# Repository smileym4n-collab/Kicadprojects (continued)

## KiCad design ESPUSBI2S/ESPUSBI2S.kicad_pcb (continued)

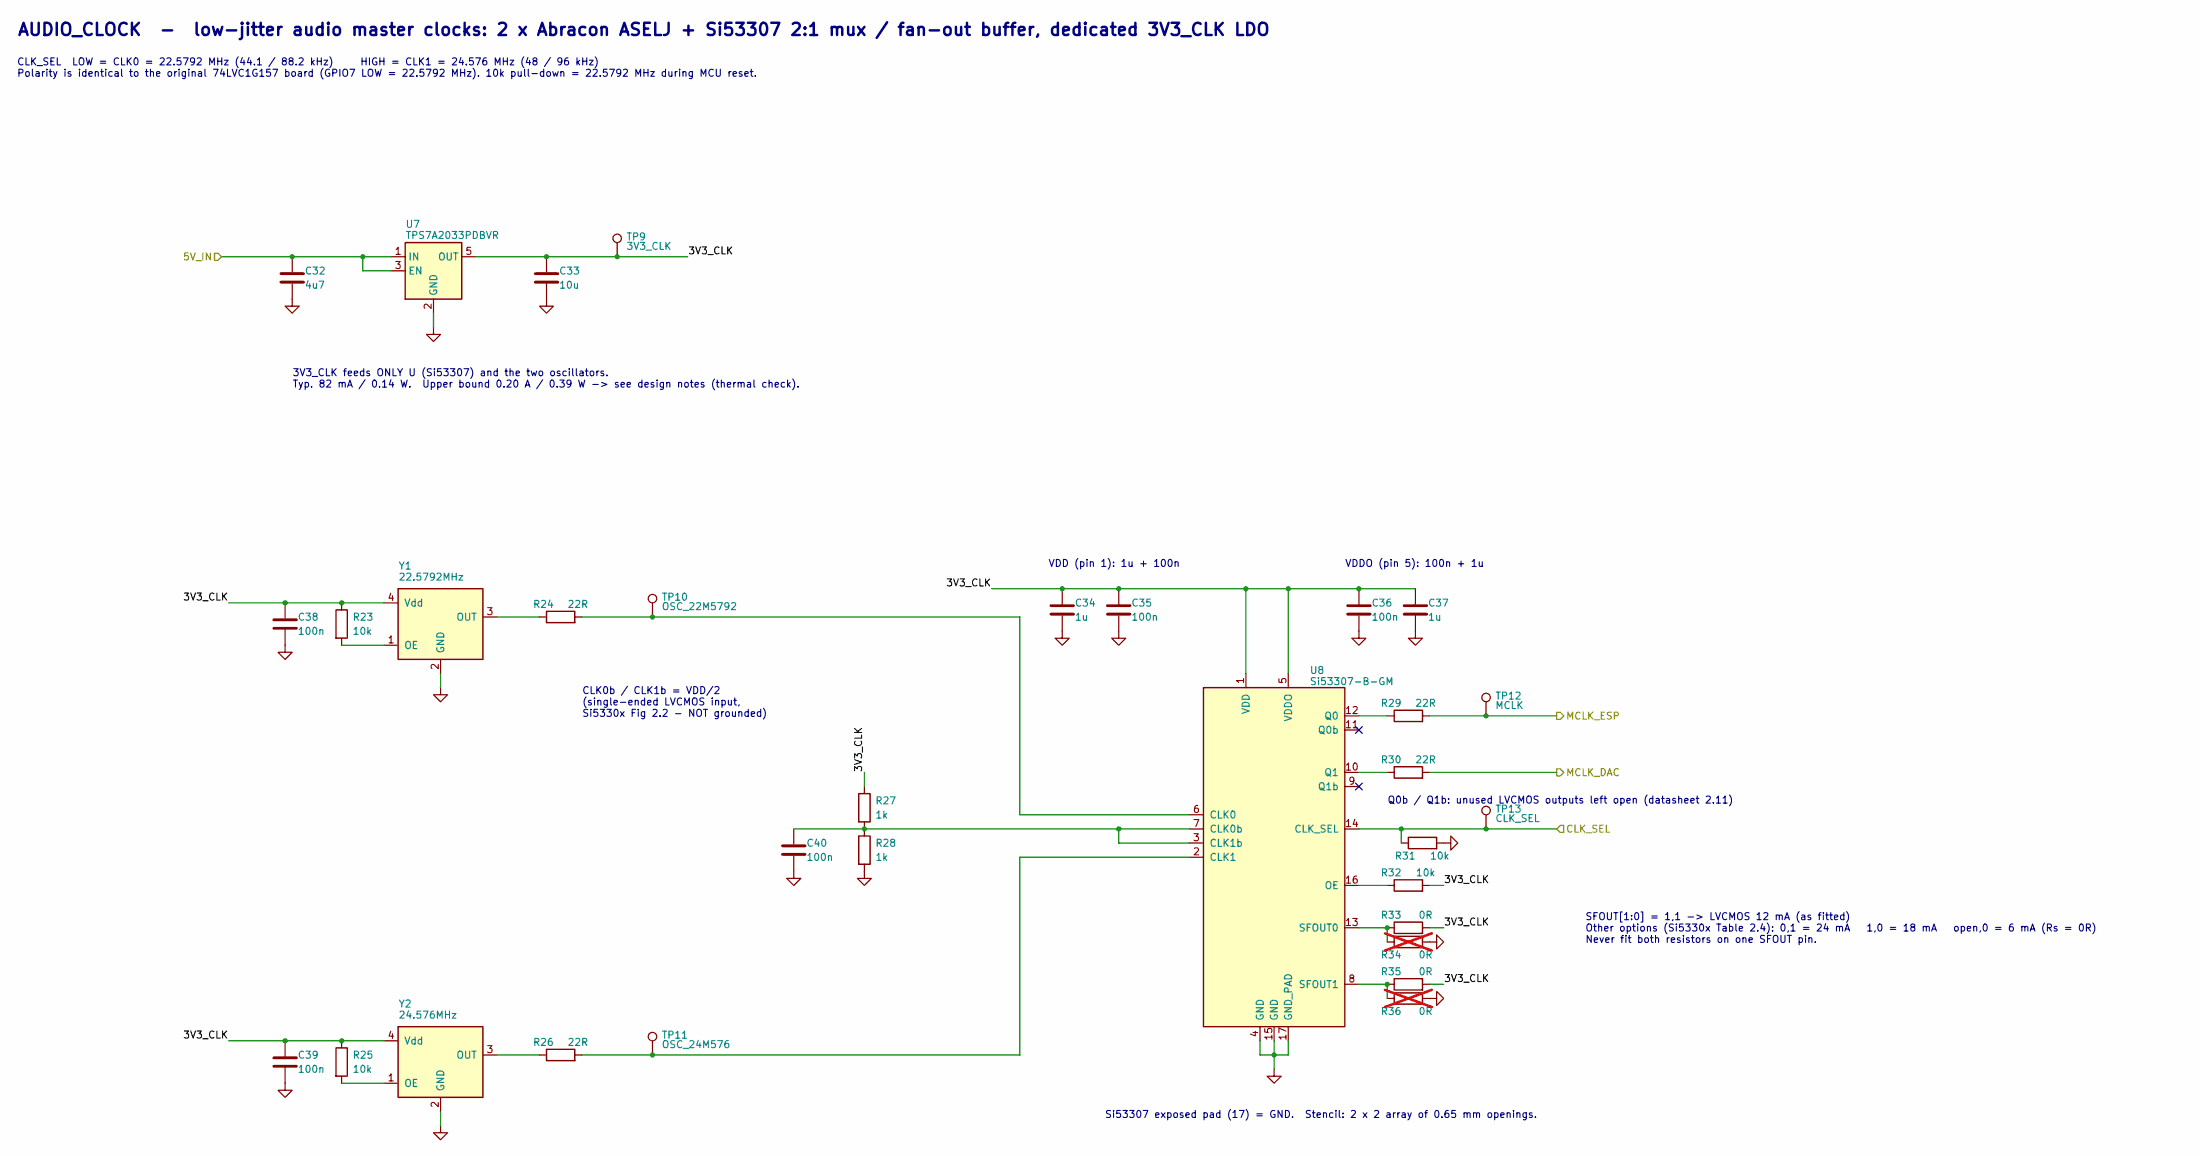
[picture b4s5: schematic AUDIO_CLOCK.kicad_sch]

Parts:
C32: 4u7; C_0805_2012Metric; MPN CL21A475KAQNNNE
C33: 10u; C_1206_3216Metric; MPN TMK316B7106KL-TD
C34, C37: 1u; C_0805_2012Metric; MPN C0805C105K3RACTU
C35, C36, C38, C39, C40: 100n; C_0603_1608Metric; MPN MC0603B104K500CT
R23, R25, R31, R32: 10k; R_0603_1608Metric; MPN RC0603FR-0710KL
R24, R26, R29, R30: 22R; R_0603_1608Metric; MPN RK73B1JTTD220J
R27, R28: 1k; R_0603_1608Metric; MPN RC0603FR-101KL
R33, R35: 0R; R_0805_2012Metric; MPN RK73Z2ATTD
R34, R36: 0R; R_0805_2012Metric; MPN RK73Z2ATTD; not fitted
TP9: 3V3_CLK; TestPoint_Pad_D1.0mm
TP10: OSC_22M5792; TestPoint_Pad_D1.0mm
TP11: OSC_24M576; TestPoint_Pad_D1.0mm
TP12: MCLK; TestPoint_Pad_D1.0mm
TP13: CLK_SEL; TestPoint_Pad_D1.0mm
U7: TPS7A2033PDBVR; SOT-23-5; MPN TPS7A2033PDBVR
U8: Si53307-B-GM; Si53307_QFN-16-1EP_3x3mm_P0.5mm_EP1.8x1.8mm; MPN Si53307-B-GM
Y1: 22.5792MHz; Abracon_ASELJ_3.2x2.5mm; MPN ASELJ-E-22.5792MHZ-L-R-T
Y2: 24.576MHz; Abracon_ASELJ_3.2x2.5mm; MPN ASELJ-E-24.576MHZ-L-R-T

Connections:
/USB_AUDIO_UAC2/5V_IN: C32.1, U7.1 (IN), U7.3 (EN); also elsewhere on the board
/USB_AUDIO_UAC2/AUDIO_CLOCK/3V3_CLK: C33.1, C34.1, C35.1, C36.1, C37.1, C38.1, C39.1, R23.1, R25.1, R27.1, R32.2, R33.2, R35.2, TP9.1 (1_1), U7.5 (OUT), U8.1 (VDD), U8.5 (VDDO), Y1.4 (Vdd), Y2.4 (Vdd)
/USB_AUDIO_UAC2/AUDIO_CLOCK/CLK_SEL: R31.1, TP13.1 (1_1), U8.14 (CLK_SEL); also elsewhere on the board
/USB_AUDIO_UAC2/AUDIO_CLOCK/MCLK_ESP: R29.2, TP12.1 (1_1); also elsewhere on the board
/USB_AUDIO_UAC2/MCLK_DAC: R30.2; also elsewhere on the board
GND: C32.2, C33.2, C34.2, C35.2, C36.2, C37.2, C38.2, C39.2, C40.2, R28.2, R31.2, R34.2, R36.2, U7.2 (GND), U8.4 (GND), U8.15 (GND), U8.17 (GND_PAD), Y1.2 (GND), Y2.2 (GND); also elsewhere on the board
unnamed: R24.2, TP10.1 (1_1), U8.6 (CLK0)
unnamed: C40.1, R27.2, R28.1, U8.3 (CLK1b), U8.7 (CLK0b)
unnamed: R26.2, TP11.1 (1_1), U8.2 (CLK1)
unnamed: R32.1, U8.16 (OE)
unnamed: R29.1, U8.12 (Q0)
unnamed: R30.1, U8.10 (Q1)
unnamed: R33.1, R34.1, U8.13 (SFOUT0)
unnamed: R35.1, R36.1, U8.8 (SFOUT1)
unnamed: R23.2, Y1.1 (OE)
unnamed: R24.1, Y1.3 (OUT)
unnamed: R25.2, Y2.1 (OE)
unnamed: R26.1, Y2.3 (OUT)

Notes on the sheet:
CLK0b / CLK1b = VDD/2 (single-ended LVCMOS input, Si5330x Fig 2.2 - NOT grounded)
AUDIO_CLOCK - low-jitter audio master clocks: 2 x Abracon ASELJ + Si53307 2:1 mux / fan-out buffer, dedicated 3V3_CLK LDO
CLK_SEL LOW = CLK0 = 22.5792 MHz (44.1 / 88.2 kHz) HIGH = CLK1 = 24.576 MHz (48 / 96 kHz) Polarity is identical to the original 74LVC1G157 board (GPIO7 LOW = 22.5792 MHz). 10k pull-down = 22.5792 MHz during MCU reset.
SFOUT[1:0] = 1,1 -> LVCMOS 12 mA (as fitted) Other options (Si5330x Table 2.4): 0,1 = 24 mA 1,0 = 18 mA open,0 = 6 mA (Rs = 0R) Never fit both resistors on one SFOUT pin.
Q0b / Q1b: unused LVCMOS outputs left open (datasheet 2.11)
VDD (pin 1): 1u + 100n
VDDO (pin 5): 100n + 1u
Si53307 exposed pad (17) = GND. Stencil: 2 x 2 array of 0.65 mm openings.
3V3_CLK feeds ONLY U (Si53307) and the two oscillators. Typ. 82 mA / 0.14 W. Upper bound 0.20 A / 0.39 W -> see design notes (thermal check).

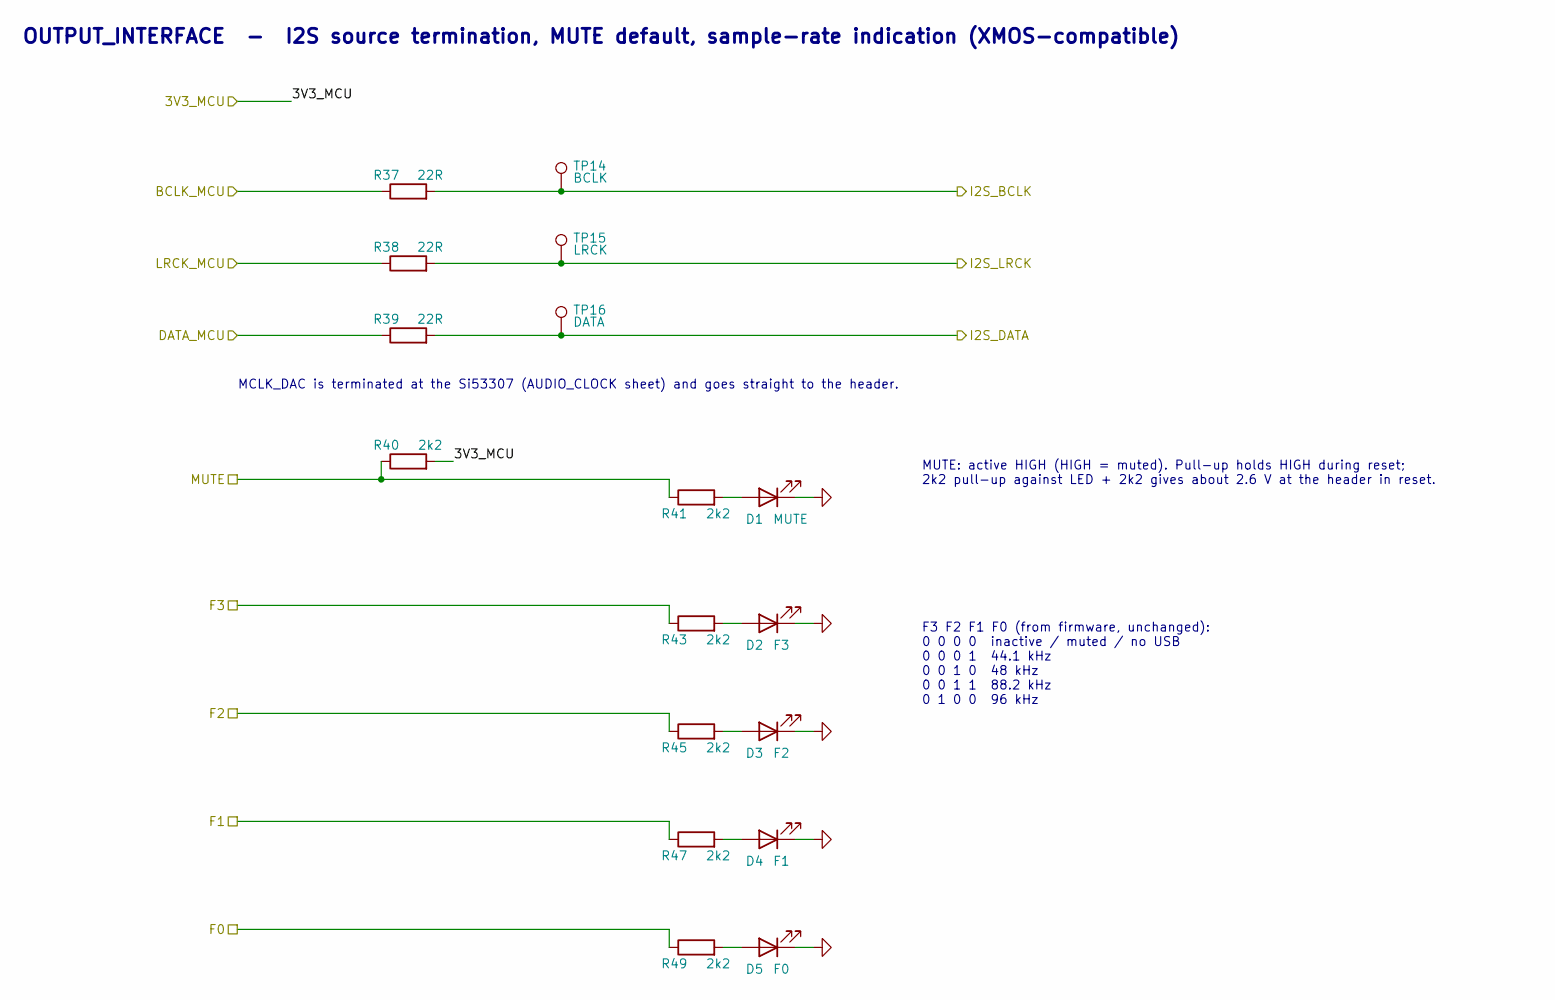
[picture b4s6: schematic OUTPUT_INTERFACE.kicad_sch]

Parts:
D1: MUTE; LED_0805_2012Metric; MPN KP-2012EC
D2: F3; LED_0805_2012Metric; MPN KP-2012EC
D3: F2; LED_0805_2012Metric; MPN KP-2012EC
D4: F1; LED_0805_2012Metric; MPN KP-2012EC
D5: F0; LED_0805_2012Metric; MPN KP-2012EC
R37, R38, R39: 22R; R_0603_1608Metric; MPN RK73B1JTTD220J
R40, R41, R43, R45, R47, R49: 2k2; R_0603_1608Metric; MPN RC0603JR-072K2L
TP14: BCLK; TestPoint_Pad_D1.0mm
TP15: LRCK; TestPoint_Pad_D1.0mm
TP16: DATA; TestPoint_Pad_D1.0mm

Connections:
/USB_AUDIO_UAC2/3V3_MCU: R40.2; also elsewhere on the board
/USB_AUDIO_UAC2/ESP32_UAC2/BCLK_MCU: R37.1; also elsewhere on the board
/USB_AUDIO_UAC2/ESP32_UAC2/DATA_MCU: R39.1; also elsewhere on the board
/USB_AUDIO_UAC2/ESP32_UAC2/LRCK_MCU: R38.1; also elsewhere on the board
/USB_AUDIO_UAC2/F0: R49.1; also elsewhere on the board
/USB_AUDIO_UAC2/F1: R47.1; also elsewhere on the board
/USB_AUDIO_UAC2/F2: R45.1; also elsewhere on the board
/USB_AUDIO_UAC2/F3: R43.1; also elsewhere on the board
/USB_AUDIO_UAC2/I2S_BCLK: R37.2, TP14.1 (1_1); also elsewhere on the board
/USB_AUDIO_UAC2/I2S_DATA: R39.2, TP16.1 (1_1); also elsewhere on the board
/USB_AUDIO_UAC2/I2S_LRCK: R38.2, TP15.1 (1_1); also elsewhere on the board
/USB_AUDIO_UAC2/MUTE: R40.1, R41.1; also elsewhere on the board
GND: D1.1 (K), D2.1 (K), D3.1 (K), D4.1 (K), D5.1 (K); also elsewhere on the board
unnamed: D1.2 (A), R41.2
unnamed: D2.2 (A), R43.2
unnamed: D3.2 (A), R45.2
unnamed: D4.2 (A), R47.2
unnamed: D5.2 (A), R49.2

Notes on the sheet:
MCLK_DAC is terminated at the Si53307 (AUDIO_CLOCK sheet) and goes straight to the header.
MUTE: active HIGH (HIGH = muted). Pull-up holds HIGH during reset; 2k2 pull-up against LED + 2k2 gives about 2.6 V at the header in reset.
F3 F2 F1 F0 (from firmware, unchanged): 0 0 0 0 inactive / muted / no USB 0 0 0 1 44.1 kHz 0 0 1 0 48 kHz 0 0 1 1 88.2 kHz 0 1 0 0 96 kHz
OUTPUT_INTERFACE - I2S source termination, MUTE default, sample-rate indication (XMOS-compatible)

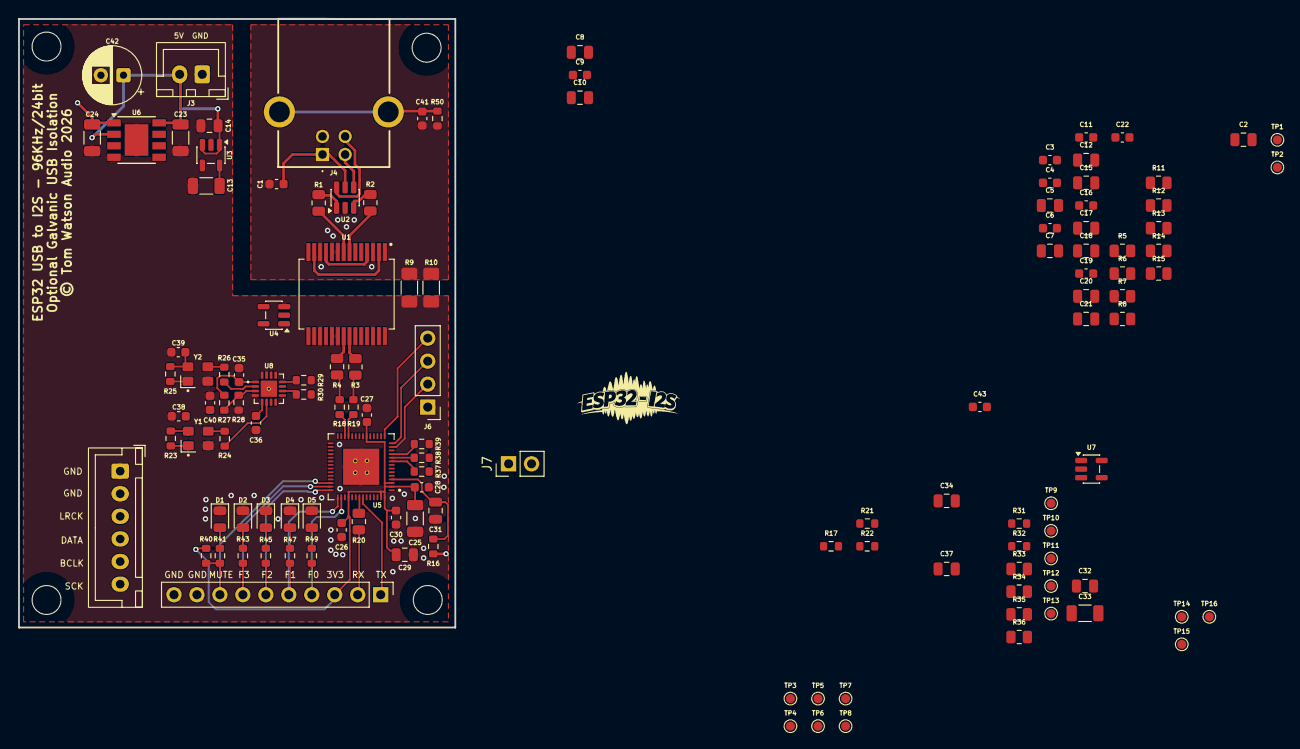
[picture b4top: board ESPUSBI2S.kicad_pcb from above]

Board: 4 copper layers, 48.3 x 67.3 mm, 130 parts (0 on the bottom side), 68 nets.

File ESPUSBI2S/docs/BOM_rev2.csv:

Refs,Qty,Value,MPN,Footprint,Config A (isolated),Config B (non-isolated),In stock,Source,Description
U1,1,ISOUSB211DPR,ISOUSB211DPR,ESPUSBI2S:ISOUSB211_DP0028A_SSOP-28_7.5x10.3mm_P0.65mm,FIT,DNP,0,BUY,"Isolated USB 2.0 HS/FS/LS repeater, 28-SSOP (DP)"
U2,1,USBLC6-2SC6,USBLC6-2SC6,Package_TO_SOT_SMD:SOT-23-6,FIT,FIT,5,inventory,"Very low capacitance ESD protection diode, 2 data-line, SOT-23-6"
C1 C26 C27 C28 C30 C35 C36 C38 C39 C40 C41 C43,12,100n,MC0603B104K500CT,Capacitor_SMD:C_0603_1608Metric,FIT,FIT,961,inventory,5 V input HF decoupling (as original board) - 100 nF 50 V X7R 1608
C2 C14,2,4u7,CL21A475KAQNNNE,Capacitor_SMD:C_0805_2012Metric,FIT,DNP,37,inventory,3V3_ISO LDO input 4.7 uF 16 V X7R - 4.7 uF 25 V X5R 2012
C3 C4 C6 C9 C11 C16 C19,7,100n,MC0603B104K500CT,Capacitor_SMD:C_0603_1608Metric,FIT,DNP,961,inventory,"V1P8V2 decoupling at pin 18 (TI 8.3: 2 uF + 0.1 uF + 10 nF, smallest closest) - 100 nF 50 V X7R 1608"
C5 C8 C17 C20,4,2u2,CL21B225KPFNNNE,Capacitor_SMD:C_0805_2012Metric,FIT,DNP,54,inventory,"V1P8V2 decoupling at pin 18 (TI 8.3: 2 uF + 0.1 uF + 10 nF, smallest closest) - 2.2 uF 10 V X7R 2012"
C7 C10 C15 C18,4,10n,0805B103K500CT,Capacitor_SMD:C_0805_2012Metric,FIT,DNP,13,inventory,"V1P8V2 decoupling at pin 18 (TI 8.3: 2 uF + 0.1 uF + 10 nF, smallest closest) - 10 nF 50 V X7R 2012"
U3,1,TPS7A2033PDBVR,TPS7A2033PDBVR,Package_TO_SOT_SMD:SOT-23-5,FIT,DNP,6,inventory,"300 mA LDO, fixed 3.3 V (ISOUSB211 local side only)"
C12,1,1u,C0805C105K3RACTU,Capacitor_SMD:C_0805_2012Metric,FIT,DNP,87,inventory,VBUS2 / VCC2 decoupling - 1 uF 25 V X7R 2012
C13,1,10u,TMK316B7106KL-TD,Capacitor_SMD:C_1206_3216Metric,FIT,DNP,43,inventory,3V3_ISO LDO output 10 uF 10 V X7R - 10 uF 25 V X7R 3216
R1 R2 R3 R4 R11,5,0R,RK73Z2ATTD,Resistor_SMD:R_0805_2012Metric,FIT,DNP,64,inventory,VBUS_DET source select: ISOUSB211 V1OK (config A)
R5 R6 R7 R8 R9 R10 R15,7,0R,RK73Z2ATTD,Resistor_SMD:R_0805_2012Metric,DNP,FIT,64,inventory,VBUS_DET source select: divider + buffer (config B)
R12,1,100k,RK73B2ATTE104J,Resistor_SMD:R_0805_2012Metric,FIT,FIT,44,inventory,VBUS_DET pull-down (defined LOW with no source link fitted)
U4,1,74LVC1G17,SN74LVC1G17DBVR,Package_TO_SOT_SMD:SOT-23-5,DNP,FIT,1,inventory,Schmitt buffer with Ioff (no back-feed into the MCU rail when local power is off)
R13,1,33k,MCWR08X3302FTL,Resistor_SMD:R_0805_2012Metric,DNP,FIT,100,inventory,VBUS divider top (the only part bridging the barrier in config B)
R14,1,47k,RMCF0805FT47K0,Resistor_SMD:R_0805_2012Metric,DNP,FIT,93,inventory,"VBUS divider bottom (ratio 0.588: 4.35 V -> 2.56 V, 5.5 V -> 3.23 V)"
C21,1,10n,0805B103K500CT,Capacitor_SMD:C_0805_2012Metric,DNP,FIT,13,inventory,VBUS detect filter - 10 nF 50 V X7R 2012
C22,1,100n,MC0603B104K500CT,Capacitor_SMD:C_0603_1608Metric,DNP,FIT,961,inventory,74LVC1G17 decoupling - 100 nF 50 V X7R 1608
U5,1,ESP32-S3-PICO-1-N8R2,ESP32-S3-PICO-1-N8R2,ESPUSBI2S:ESP32-S3-PICO-1_LGA-56-1EP_7x7mm_P0.4mm,FIT,FIT,,BUY,"ESP32-S3 SiP, 8 MB quad flash, 2 MB quad PSRAM, 40 MHz crystal, LGA56 7x7 mm"
U6,1,AP7361C-33SP-13,AP7361C-33SP-13,Package_SO:Diodes_SO-8EP,FIT,FIT,,BUY,"1 A LDO, fixed 3.3 V, enable, SO-8EP"
C23 C25 C33,3,10u,TMK316B7106KL-TD,Capacitor_SMD:C_1206_3216Metric,FIT,FIT,43,inventory,10 uF 10 V X7R - 10 uF 25 V X7R 3216
C24,1,22u,EMK316BB7226ML-T,Capacitor_SMD:C_1206_3216Metric,FIT,FIT,,BUY,22 uF 16 V X7R 3216 (regulator output) - 22 uF 16 V X7R 3216
C29 C31 C34 C37,4,1u,C0805C105K3RACTU,Capacitor_SMD:C_0805_2012Metric,FIT,FIT,87,inventory,1 uF 16 V X7R - at VDDO pin 5 - 1 uF 25 V X7R 2012
R16 R17 R21 R22 R23 R25 R31 R32 R42 R44 R46 R48,12,10k,RC0603FR-0710KL,Resistor_SMD:R_0603_1608Metric,FIT,FIT,53,inventory,Sample-rate line pull-down: 0000 (inactive) while the MCU is in reset (new in rev 2)
R18 R19 R24 R26 R29 R30 R37 R38 R39,9,22R,RK73B1JTTD220J,Resistor_SMD:R_0603_1608Metric,FIT,FIT,139,inventory,I2S source termination - place at the MCU pin (as original board)
R20,1,470R,ASC0805-470RFT5,Resistor_SMD:R_0805_2012Metric,FIT,FIT,86,inventory,U0TXD series resistor (Espressif guideline suggests 499R; 470R from stock)
U7,1,TPS7A2033PDBVR,TPS7A2033PDBVR,Package_TO_SOT_SMD:SOT-23-5,FIT,FIT,6,inventory,"300 mA low-noise LDO, fixed 3.3 V (clock rail only)"
C32,1,4u7,CL21A475KAQNNNE,Capacitor_SMD:C_0805_2012Metric,FIT,FIT,37,inventory,4.7 uF 16 V X7R - 4.7 uF 25 V X5R 2012
U8,1,Si53307-B-GM,Si53307-B-GM,ESPUSBI2S:Si53307_QFN-16-1EP_3x3mm_P0.5mm_EP1.8x1.8mm,FIT,FIT,,BUY,"2:1 glitchless clock mux + 2-output universal buffer, low additive jitter, 16-QFN 3x3 mm"
Y1,1,22.5792MHz,ASELJ-E-22.5792MHZ-L-R-T,ESPUSBI2S:Abracon_ASELJ_3.2x2.5mm,FIT,FIT,,BUY,"Low-jitter 3.3 V CMOS crystal oscillator, 3.2 x 2.5 mm, OE active high (open = enabled)"
Y2,1,24.576MHz,ASELJ-E-24.576MHZ-L-R-T,ESPUSBI2S:Abracon_ASELJ_3.2x2.5mm,FIT,FIT,,BUY,"Low-jitter 3.3 V CMOS crystal oscillator, 3.2 x 2.5 mm, OE active high (open = enabled)"
R27 R28,2,1k,RC0603FR-101KL,Resistor_SMD:R_0603_1608Metric,FIT,FIT,99,inventory,CLK0b/CLK1b bias divider to VDD/2 (Si5330x Fig 2.2)
R33 R35,2,0R,RK73Z2ATTD,Resistor_SMD:R_0805_2012Metric,FIT,FIT,64,inventory,SFOUT1 strap HIGH (fitted): LVCMOS 12 mA drive with SFOUT[1:0] = 11
R34 R36,2,0R,RK73Z2ATTD,Resistor_SMD:R_0805_2012Metric,DNP (option),DNP (option),64,inventory,SFOUT1 strap LOW (alternative drive strength) - DNP
R40 R41 R43 R45 R47 R49,6,2k2,RC0603JR-072K2L,Resistor_SMD:R_0603_1608Metric,FIT,FIT,37,inventory,LED current limit (as original board)
D1,1,MUTE,KP-2012EC,LED_SMD:LED_0805_2012Metric,FIT,FIT,9,inventory,"Red indicator LED 2012, Kingbright KP-2012EC (optional - DNP for integrated use)"
D2,1,F3,KP-2012EC,LED_SMD:LED_0805_2012Metric,FIT,FIT,9,inventory,"Red indicator LED 2012, Kingbright KP-2012EC (optional - DNP for integrated use)"
D3,1,F2,KP-2012EC,LED_SMD:LED_0805_2012Metric,FIT,FIT,9,inventory,"Red indicator LED 2012, Kingbright KP-2012EC (optional - DNP for integrated use)"
D4,1,F1,KP-2012EC,LED_SMD:LED_0805_2012Metric,FIT,FIT,9,inventory,"Red indicator LED 2012, Kingbright KP-2012EC (optional - DNP for integrated use)"
D5,1,F0,KP-2012EC,LED_SMD:LED_0805_2012Metric,FIT,FIT,9,inventory,"Red indicator LED 2012, Kingbright KP-2012EC (optional - DNP for integrated use)"
J1,1,I2S OUT,,Connector_JST:JST_XH_B6B-XH-A_1x06_P2.50mm_Vertical,FIT,FIT,,not tracked in inventory,Connector (pin-out unchanged from the original board)
J2,1,STATUS / UART,,Connector_PinHeader_2.54mm:PinHeader_1x10_P2.54mm_Vertical,FIT,FIT,,not tracked in inventory,Connector (pin-out unchanged from the original board)
J6,1,COMM,,Connector_PinHeader_2.54mm:PinHeader_1x04_P2.54mm_Vertical,FIT,FIT,,not tracked in inventory,Connector (pin-out unchanged from the original board)
J7,1,BOOT,,Connector_PinHeader_2.54mm:PinHeader_1x02_P2.54mm_Vertical,FIT,FIT,,not tracked in inventory,"BOOT jumper: 2-pin 2.54 mm header, GPIO0 to GND; fit shunt while applying power for ROM download mode"
J4,1,USB CONNECTOR,,Custom:USBC,FIT,FIT,,not tracked in inventory,USB receptacle (footprint and pin mapping unchanged from the original board)
R50,1,1M,RC0603FR-101ML,Resistor_SMD:R_0603_1608Metric,FIT,FIT,90,inventory,USB shield bleed to GND_USB (as original board)
J3,1,POWER IN 5V,,Connector_JST:JST_XH_B2B-XH-A_1x02_P2.50mm_Vertical,FIT,FIT,,not tracked in inventory,"Regulated 5 V DC input (pin 1 GND, pin 2 +5 V - unchanged)"
C42,1,220u,EEUFR1C221B,Capacitor_THT:CP_Radial_D6.3mm_P2.50mm,FIT,FIT,10,inventory,"5 V input reservoir 220 uF 16 V Panasonic FR, 6.3 x 11.2 mm (as original board)"

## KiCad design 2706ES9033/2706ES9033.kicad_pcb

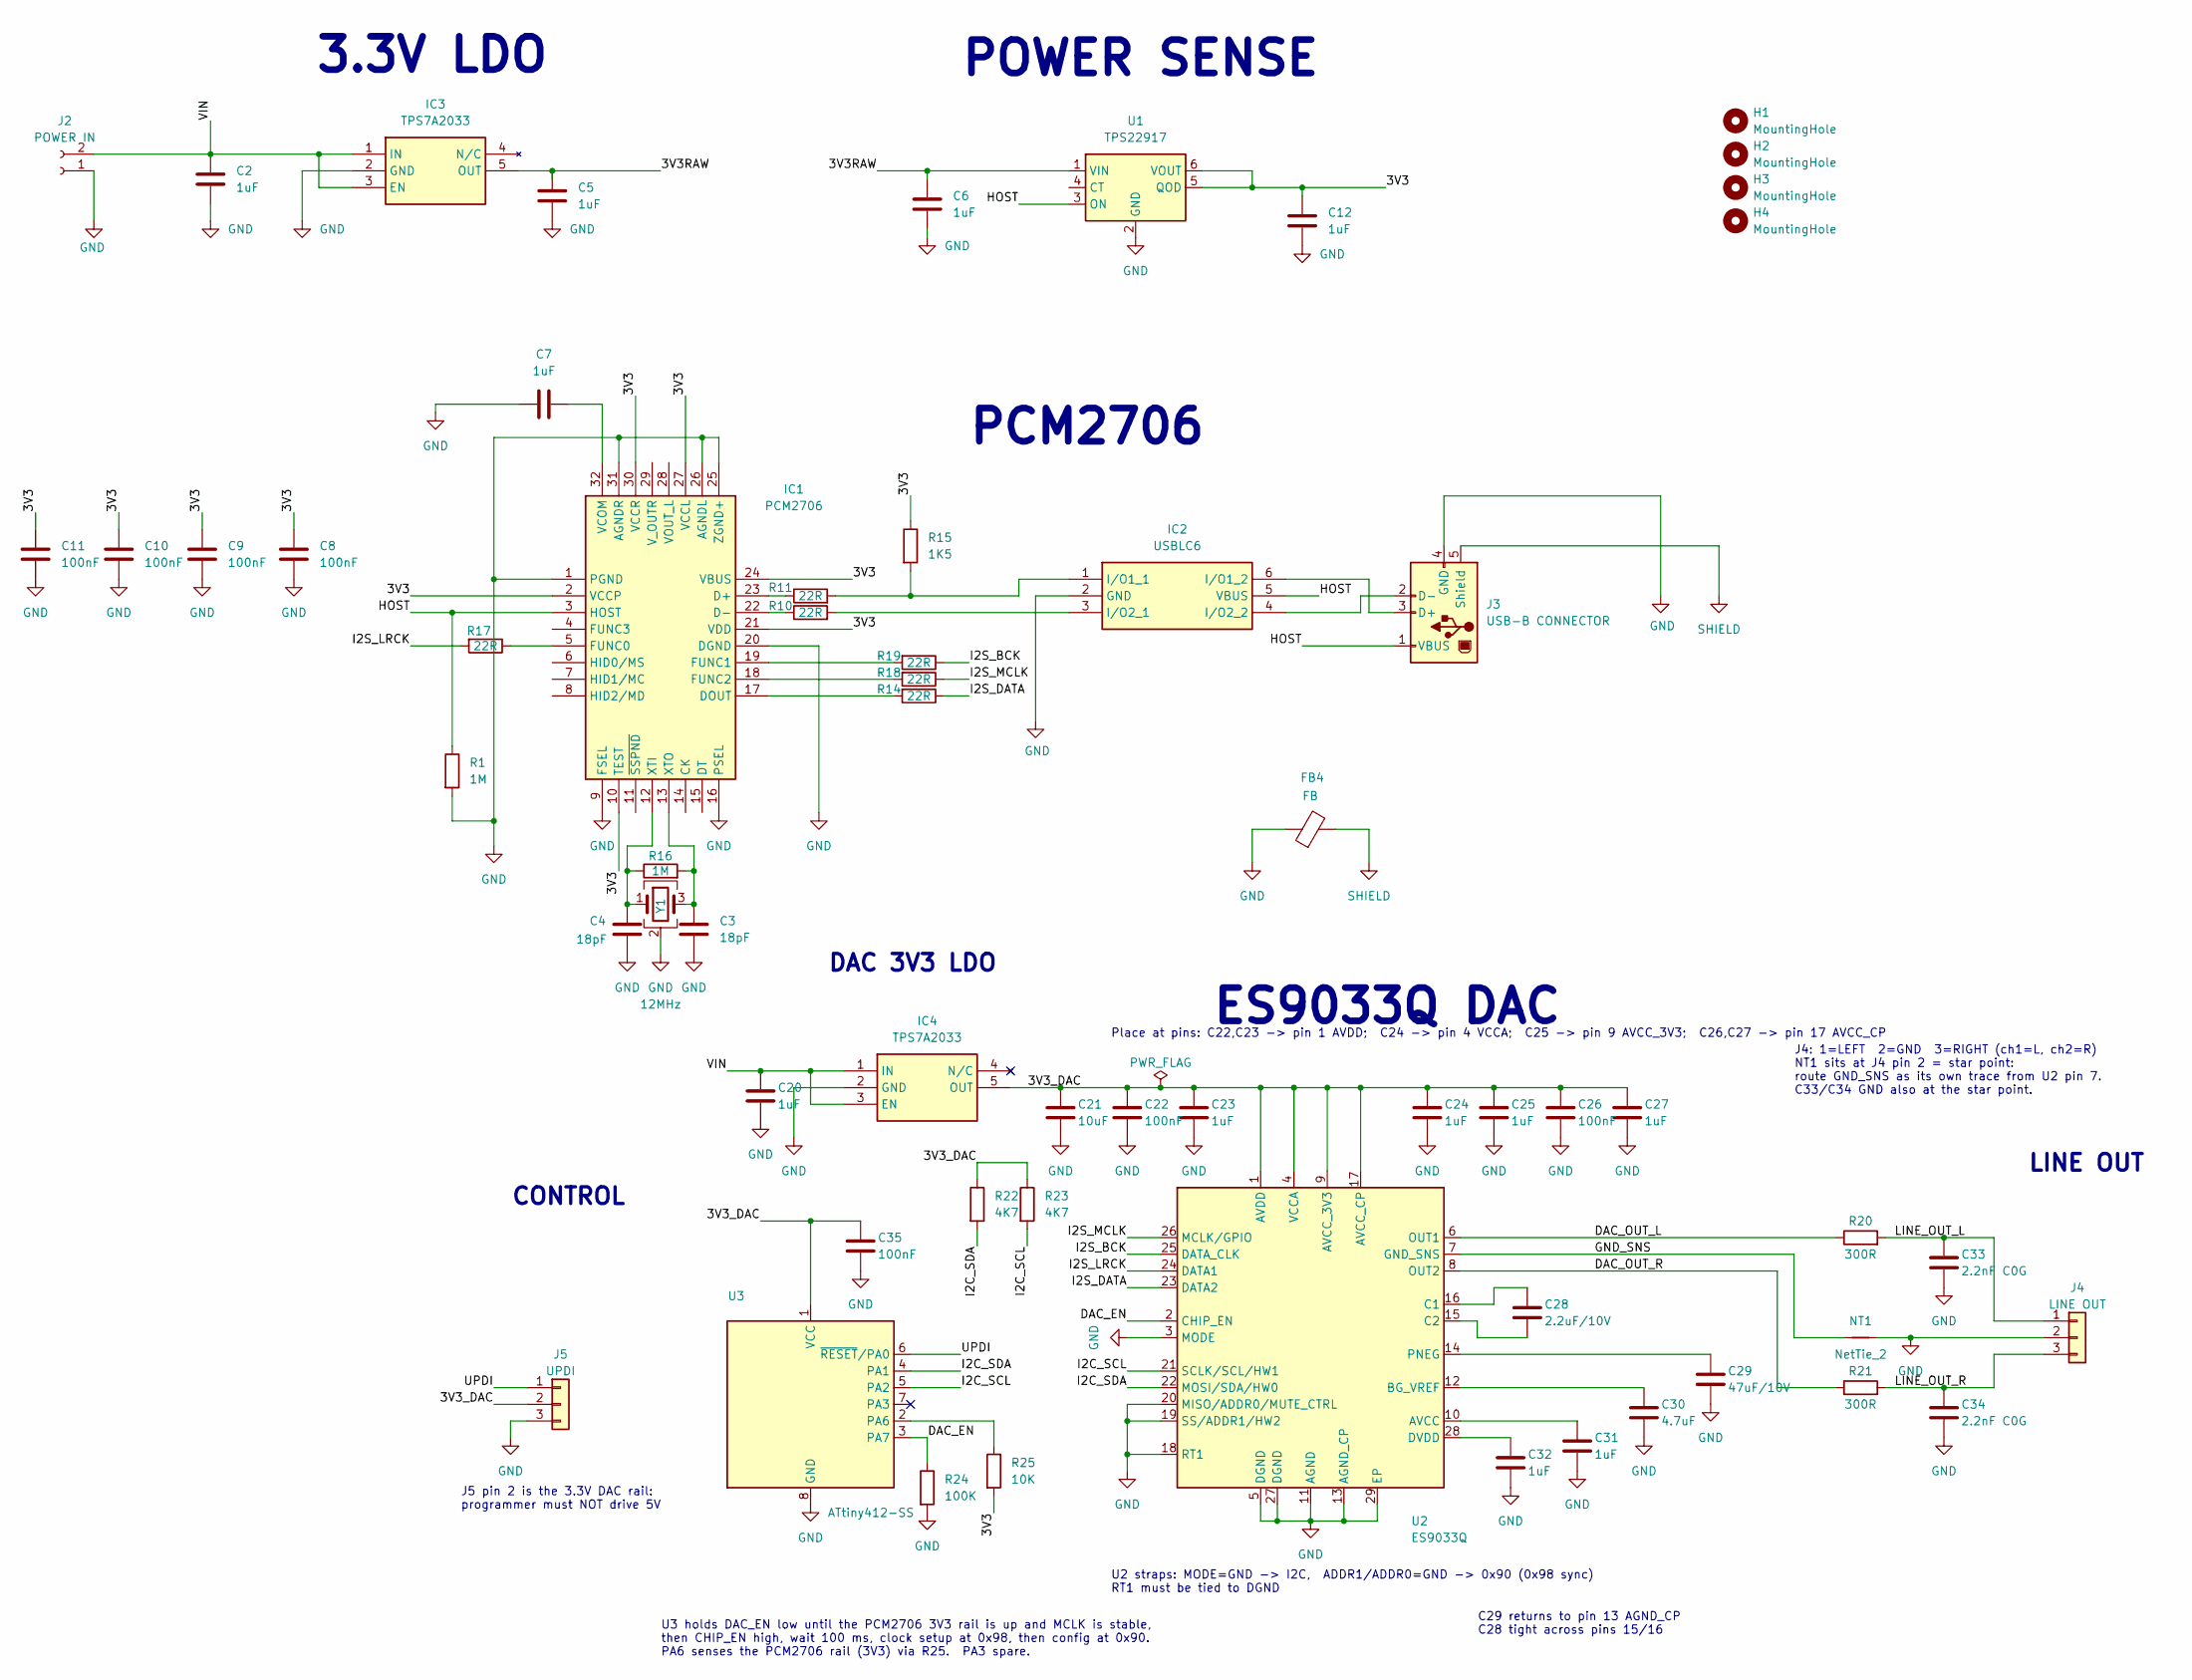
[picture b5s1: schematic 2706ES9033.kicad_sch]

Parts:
C2, C5, C6, C7, C12: 1uF; C_0805_2012Metric_Pad1.18x1.45mm_HandSolder
C3, C4: 18pF; C_0603_1608Metric_Pad1.08x0.95mm_HandSolder
C8, C9, C10, C11: 100nF; C_0603_1608Metric_Pad1.08x0.95mm_HandSolder
C20, C23, C24, C25, C27, C31, C32: 1uF; C_0805_2012Metric_Pad1.18x1.45mm_HandSolder; MPN C0805C105K3RACTU
C21: 10uF; C_1206_3216Metric_Pad1.33x1.80mm_HandSolder; MPN TMK316B7106KL-TD
C22, C26, C35: 100nF; C_0603_1608Metric_Pad1.08x0.95mm_HandSolder; MPN MC0603B104K500CT
C28: 2.2uF/10V; C_0805_2012Metric_Pad1.18x1.45mm_HandSolder; MPN CL21B225KPFNNNE
C29: 47uF/10V; C_1206_3216Metric_Pad1.33x1.80mm_HandSolder; MPN CL31A476MPHNNNE
C30: 4.7uF; C_0805_2012Metric_Pad1.18x1.45mm_HandSolder; MPN CL21A475KAQNNNE
C33, C34: 2.2nF C0G; C_0805_2012Metric_Pad1.18x1.45mm_HandSolder; MPN GCM2165C2A222FA16D
FB4: FB; L_1206_3216Metric_Pad1.42x1.75mm_HandSolder
H1, H2, H3, H4: MountingHole; MountingHole_3.2mm_M3
IC1: PCM2706; PCM2706C; Mouser Part Number 595-PCM2706CPJTR
IC2: USBLC6; SOT-23-6_Handsoldering; Mouser Part Number 511-USBLC6-2SC6
IC3: TPS7A2033; SOT95P280X145-5N; Mouser Part Number 595-TPS7A2033PDBVR
IC4: TPS7A2033; SOT95P280X145-5N; MPN TPS7A2033PDBVR
J2: POWER IN; JST_XH_B2B-XH-A_1x02_P2.50mm_Vertical
J3: USB-B CONNECTOR; USBC
J4: LINE OUT; Molex_KK-254_AE-6410-03A_1x03_P2.54mm_Vertical; MPN MC34631
J5: UPDI; Molex_KK-254_AE-6410-03A_1x03_P2.54mm_Vertical; MPN MC34631
NT1: NetTie_2; NetTie-2_SMD_Pad0.5mm
R1, R16: 1M; R_0603_1608Metric_Pad0.98x0.95mm_HandSolder
R10, R11, R14, R17, R18, R19: 22R; R_0603_1608Metric_Pad0.98x0.95mm_HandSolder
R15: 1K5; R_0603_1608Metric_Pad0.98x0.95mm_HandSolder
R20, R21: 300R; R_0805_2012Metric_Pad1.20x1.40mm_HandSolder; MPN ERA-6AEB301V
R22, R23: 4K7; R_0805_2012Metric_Pad1.20x1.40mm_HandSolder; MPN RMCF0805FT4K70
R24: 100K; R_0805_2012Metric_Pad1.20x1.40mm_HandSolder; MPN RK73B2ATTE104J
R25: 10K; R_0805_2012Metric_Pad1.20x1.40mm_HandSolder; MPN RK73B2ATTD103J
U1: TPS22917; SOT-23-6
U2: ES9033Q; ESS_QFN-28-1EP_5x5mm_P0.5mm_EP3.15x3.15mm; MPN ES9033Q
U3: ATtiny412-SS; SOIC-8_3.9x4.9mm_P1.27mm; MPN ATTINY412-SSN
Y1: 12MHz; Crystal_SMD_3225-4Pin_3.2x2.5mm; MPN 830108338809; Mouser Part Number 710-830108338809

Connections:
/3V3: C8.1, C9.1, C10.1, C11.1, C12.1, IC1.2 (VCCP), IC1.10 (TEST), IC1.21 (VDD), IC1.24 (VBUS), IC1.27 (VCCL), IC1.30 (VCCR), R15.1, R25.2, U1.5 (QOD), U1.6 (VOUT)
/3V3RAW: C5.1, C6.1, IC3.5 (OUT), U1.1 (VIN)
/3V3_DAC: C21.1, C22.1, C23.1, C24.1, C25.1, C26.1, C27.1, C35.1, IC4.5 (OUT), J5.2, R22.1, R23.1, U2.1 (AVDD), U2.4 (VCCA), U2.9 (AVCC_3V3), U2.17 (AVCC_CP), U3.1 (VCC)
/DAC_EN: R24.1, U2.2 (CHIP_EN), U3.3 (PA7)
/DAC_OUT_L: R20.1, U2.6 (OUT1)
/DAC_OUT_R: R21.1, U2.8 (OUT2)
/GND_SNS: NT1.1, U2.7 (GND_SNS)
/HOST: IC1.3 (HOST), IC2.5 (VBUS), J3.1 (VBUS), R1.1, U1.3 (ON)
/I2C_SCL: R23.2, U2.21 (SCLK/SCL/HW1), U3.5 (PA2)
/I2C_SDA: R22.2, U2.22 (MOSI/SDA/HW0), U3.4 (PA1)
/I2S_BCK: R19.1, U2.25 (DATA_CLK)
/I2S_DATA: R14.1, U2.23 (DATA2)
/I2S_LRCK: R17.2, U2.24 (DATA1)
/I2S_MCLK: R18.1, U2.26 (MCLK/GPIO)
/LINE_OUT_L: C33.1, J4.1, R20.2
/LINE_OUT_R: C34.1, J4.3, R21.2
/UPDI: J5.1, U3.6 (~RESET/PA0)
/VIN: C2.1, C20.1, IC3.1 (IN), IC3.3 (EN), IC4.1 (IN), IC4.3 (EN), J2.2
GND: C2.2, C3.2, C4.2, C5.2, C6.2, C7.1, C8.2, C9.2, C10.2, C11.2, C12.2, C20.2, C21.2, C22.2, C23.2, C24.2, C25.2, C26.2, C27.2, C29.2, C30.2, C31.2, C32.2, C33.2, C34.2, C35.2, FB4.1, IC1.1 (PGND), IC1.9 (FSEL), IC1.16 (PSEL), IC1.20 (DGND), IC1.25 (ZGND+), IC1.26 (AGNDL), IC1.31 (AGNDR), IC2.2 (GND), IC3.2 (GND), IC4.2 (GND), J2.1, J3.4 (GND), J4.2, J5.3, NT1.2, R1.2, R24.2, U1.2 (GND), U2.3 (MODE), U2.5 (DGND), U2.11 (AGND), U2.13 (AGND_CP), U2.18 (RT1), U2.19 (SS/ADDR1/HW2), U2.20 (MISO/ADDR0/MUTE_CTRL), U2.27 (DGND), U2.29 (EP), U3.8 (GND), Y1.2 (G), Y1.4 (G)
unnamed: IC1.23 (D+), R11.1
unnamed: IC1.22 (D-), R10.1
unnamed: IC1.17 (DOUT), R14.2
unnamed: IC1.5 (FUNC0), R17.1
unnamed: IC1.19 (FUNC1), R19.2
unnamed: IC1.18 (FUNC2), R18.2
unnamed: C7.2, IC1.32 (VCOM)
unnamed: C4.1, IC1.12 (XTI), R16.1, Y1.1
unnamed: C3.1, IC1.13 (XTO), R16.2, Y1.3
unnamed: IC2.1 (I/O1_1), R11.2, R15.2
unnamed: IC2.6 (I/O1_2), J3.3 (D+)
unnamed: IC2.3 (I/O2_1), R10.2
unnamed: IC2.4 (I/O2_2), J3.2 (D-)
unnamed: C31.1, U2.10 (AVCC)
unnamed: C30.1, U2.12 (BG_VREF)
unnamed: C28.1, U2.16 (C1)
unnamed: C28.2, U2.15 (C2)
unnamed: C32.1, U2.28 (DVDD)
unnamed: C29.1, U2.14 (PNEG)
unnamed: R25.1, U3.2 (PA6)
SHIELD: FB4.2, J3.5 (Shield)

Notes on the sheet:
3.3V LDO
ES9033Q DAC
U3 holds DAC_EN low until the PCM2706 3V3 rail is up and MCLK is stable, then CHIP_EN high, wait 100 ms, clock setup at 0x98, then config at 0x90. PA6 senses the PCM2706 rail (3V3) via R25. PA3 spare.
J4: 1=LEFT 2=GND 3=RIGHT (ch1=L, ch2=R) NT1 sits at J4 pin 2 = star point: route GND_SNS as its own trace from U2 pin 7. C33/C34 GND also at the star point.
U2 straps: MODE=GND -> I2C, ADDR1/ADDR0=GND -> 0x90 (0x98 sync) RT1 must be tied to DGND
PCM2706
CONTROL
POWER SENSE
Place at pins: C22,C23 -> pin 1 AVDD; C24 -> pin 4 VCCA; C25 -> pin 9 AVCC_3V3; C26,C27 -> pin 17 AVCC_CP
LINE OUT
C29 returns to pin 13 AGND_CP C28 tight across pins 15/16
J5 pin 2 is the 3.3V DAC rail: programmer must NOT drive 5V
DAC 3V3 LDO

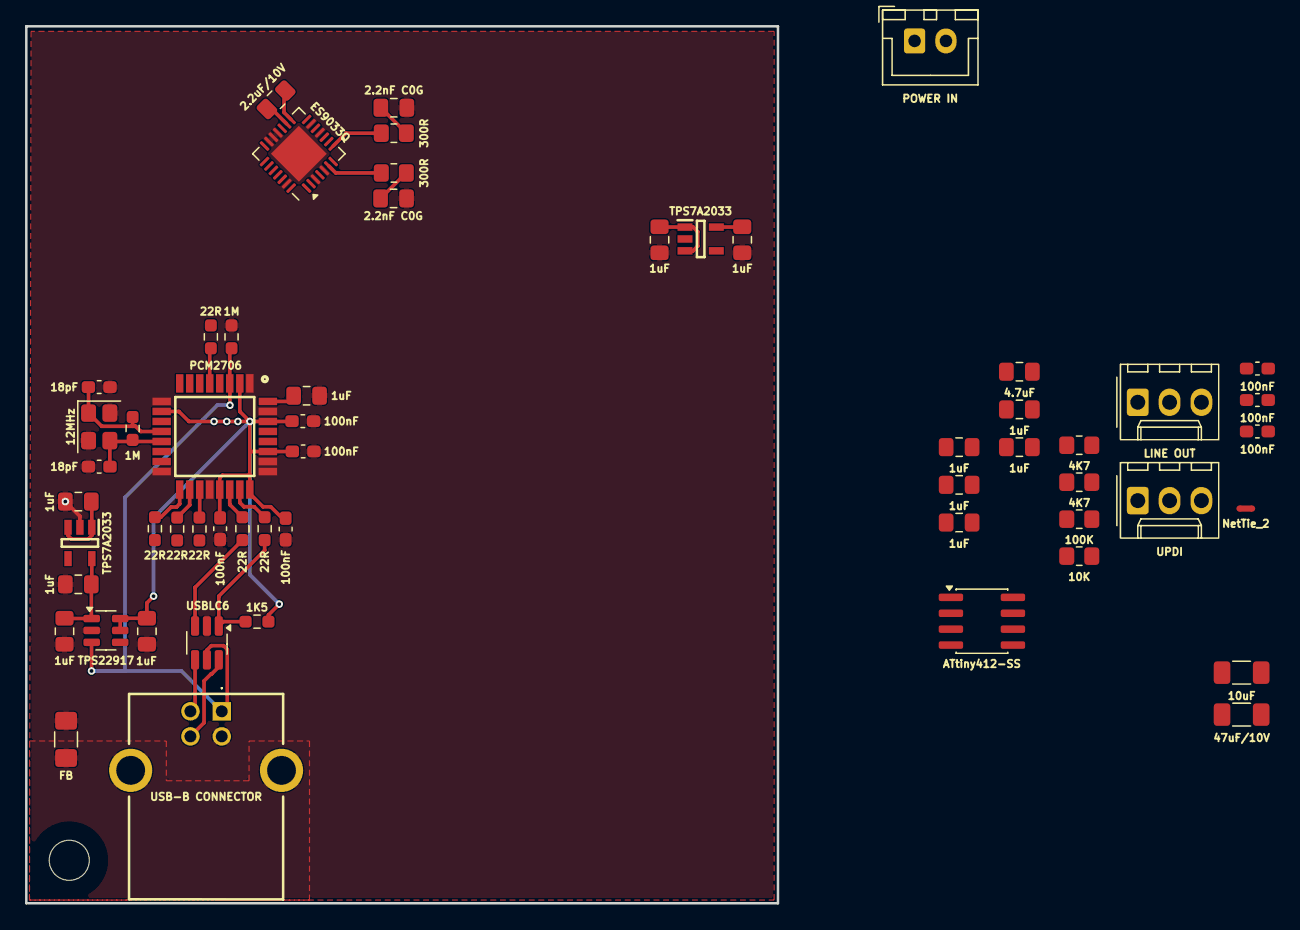
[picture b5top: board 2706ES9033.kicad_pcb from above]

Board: 2 copper layers, 60.0 x 70.0 mm, 60 parts (0 on the bottom side), 40 nets.
